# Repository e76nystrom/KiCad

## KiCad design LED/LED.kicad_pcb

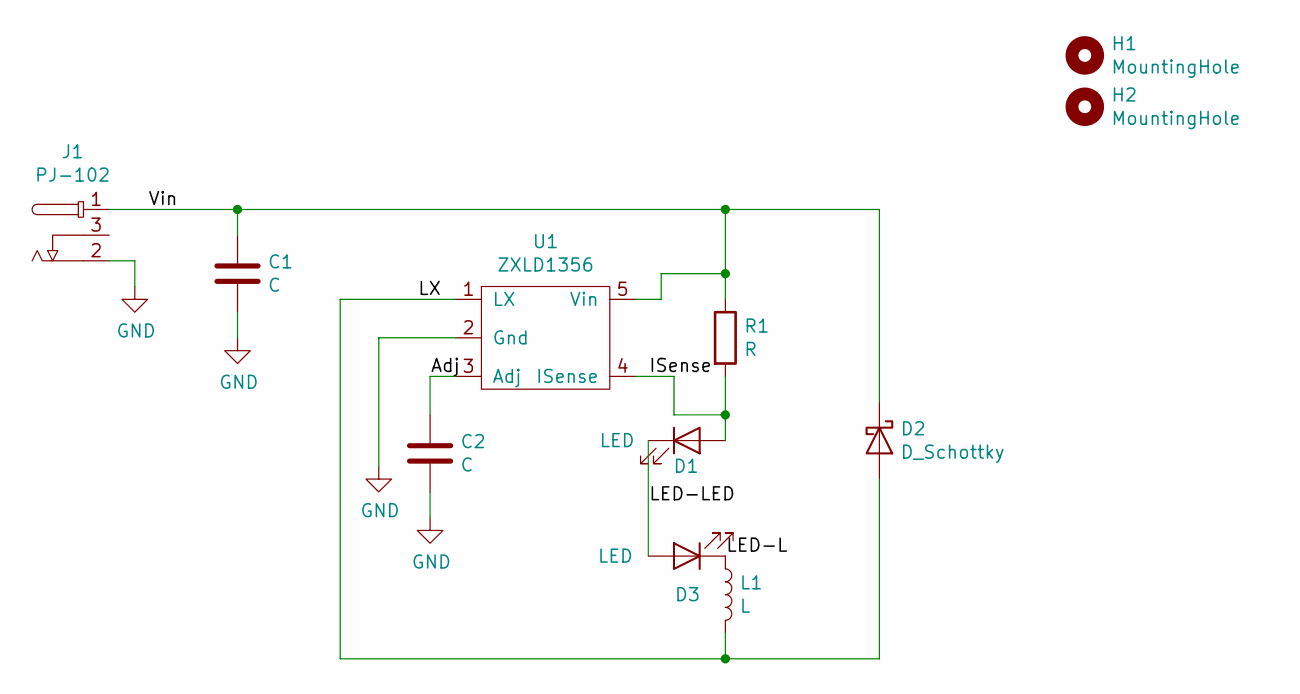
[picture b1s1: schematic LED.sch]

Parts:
C1, C2: C; C_0805_2012Metric_Pad1.15x1.40mm_HandSolder
D1, D3: LED; XT-LED
D2: D_Schottky; D_SMB_Handsoldering
H1, H2: MountingHole; MountingHole _1-8_1-4
J1: PJ-102
L1: L; SDR-1006
R1: R; R_0805_2012Metric_Pad1.15x1.40mm_HandSolder
U1: ZXLD1356; SOT-23-5

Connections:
/Adj: C2.1, U1.3 (Adj)
/ISense: D1.2 (A), R1.2, U1.4 (ISense)
/LED-L: D3.1 (K), L1.1
/LED-LED: D1.1 (K), D3.2 (A)
/LX: D2.2 (A), L1.2, U1.1 (LX)
/Vin: C1.1, D2.1 (K), J1.1, R1.1, U1.5 (Vin)
GND: C1.2, C2.2, J1.2, U1.2 (Gnd)

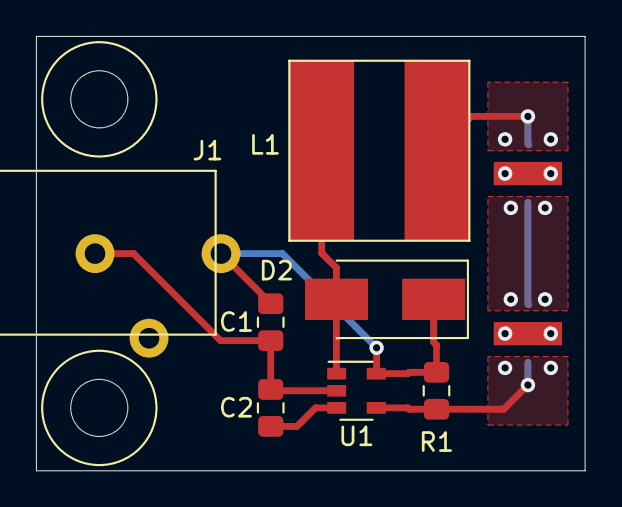
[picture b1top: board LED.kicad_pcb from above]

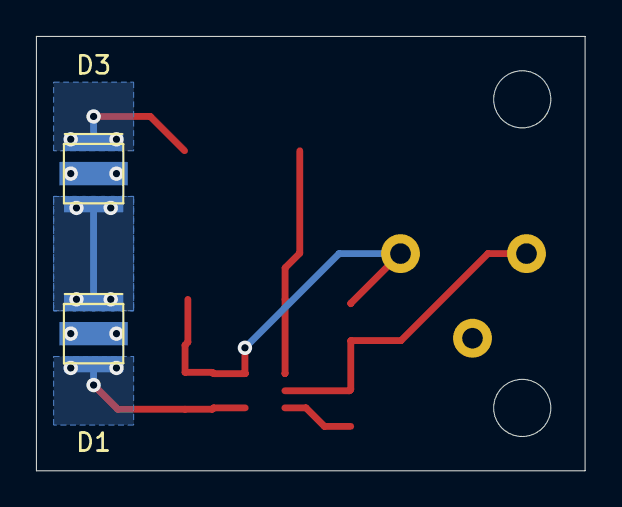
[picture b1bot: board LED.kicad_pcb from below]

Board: 2 copper layers, 30.5 x 24.1 mm, 11 parts (2 on the bottom side), 7 nets.

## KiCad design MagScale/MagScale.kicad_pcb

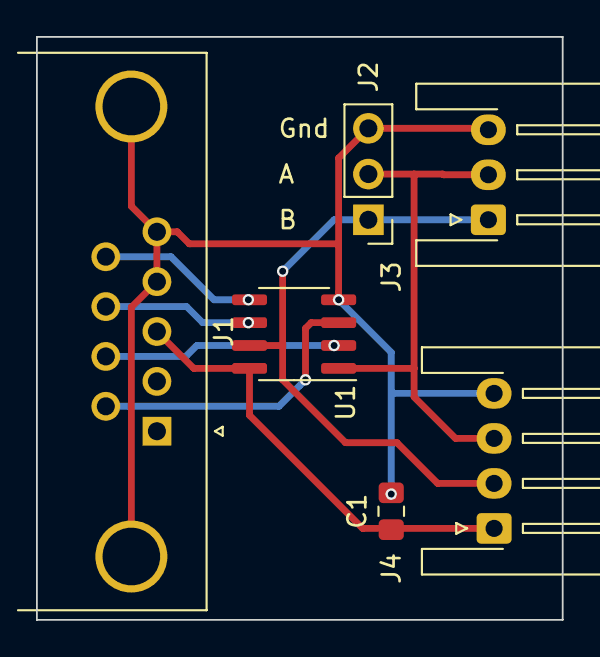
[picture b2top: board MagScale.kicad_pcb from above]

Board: 2 copper layers, 29.2 x 32.4 mm, 6 parts (0 on the bottom side), 8 nets.

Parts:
C1: C; C_0805_2012Metric_Pad1.15x1.40mm_HandSolder
J1: DB9_Female_MountingHoles; DSUB-9_Female_Horizontal_P2.77x2.84mm_EdgePinOffset4.94mm_H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
J2: Conn_01x03_Male; PinHeader_1x03_P2.54mm_Vertical
J3: Conn_01x03; JST_XH_S3B-XH-A-1_1x03_P2.50mm_Horizontal
J4: Conn_01x04; JST_XH_S4B-XH-A-1_1x04_P2.50mm_Horizontal
U1: OP275; SOIC-8_3.9x4.9mm_P1.27mm

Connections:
+5V: C1.1, J1.3, J4.1, U1.8
/A: J2.2, J3.2, J4.3, U1.1
/A+: J1.6, U1.3
/A-: J1.7, U1.2
/B: J2.1, J3.1, J4.2, U1.7
/B+: J1.9, U1.5
/B-: J1.8, U1.6
GND: C1.2, J1.0, J1.4, J1.5, J2.3, J3.3, J4.4, U1.4

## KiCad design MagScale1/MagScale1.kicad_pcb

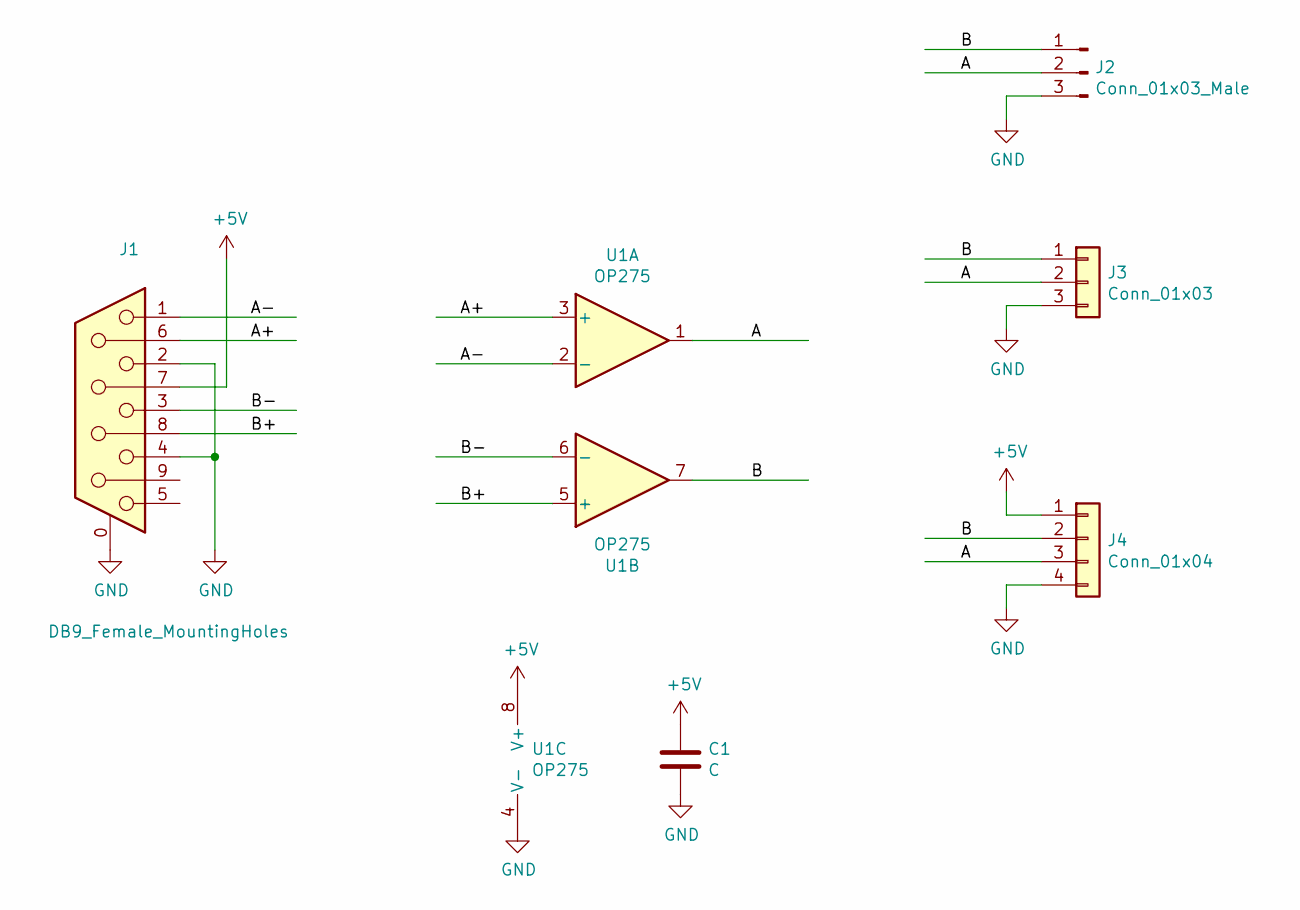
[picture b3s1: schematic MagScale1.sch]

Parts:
C1: C; C_0805_2012Metric_Pad1.15x1.40mm_HandSolder
J1: DB9_Female_MountingHoles; DSUB-9_Female_Horizontal_P2.77x2.84mm_EdgePinOffset4.94mm_H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
J2: Conn_01x03_Male; PinHeader_1x03_P2.54mm_Vertical
J3: Conn_01x03; JST_XH_S3B-XH-A-1_1x03_P2.50mm_Horizontal
J4: Conn_01x04; JST_XH_S4B-XH-A-1_1x04_P2.50mm_Horizontal
U1: OP275; SOIC-8_3.9x4.9mm_P1.27mm

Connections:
+5V: C1.1, J1.7, J4.1, U1.8 (V+)
/A: J2.2, J3.2, J4.3, U1.1
/A+: J1.6, U1.3 (+)
/A-: J1.1, U1.2 (-)
/B: J2.1, J3.1, J4.2, U1.7
/B+: J1.8, U1.5 (+)
/B-: J1.3, U1.6 (-)
GND: C1.2, J1.0 (PAD), J1.2, J1.4, J2.3, J3.3, J4.4, U1.4 (V-)

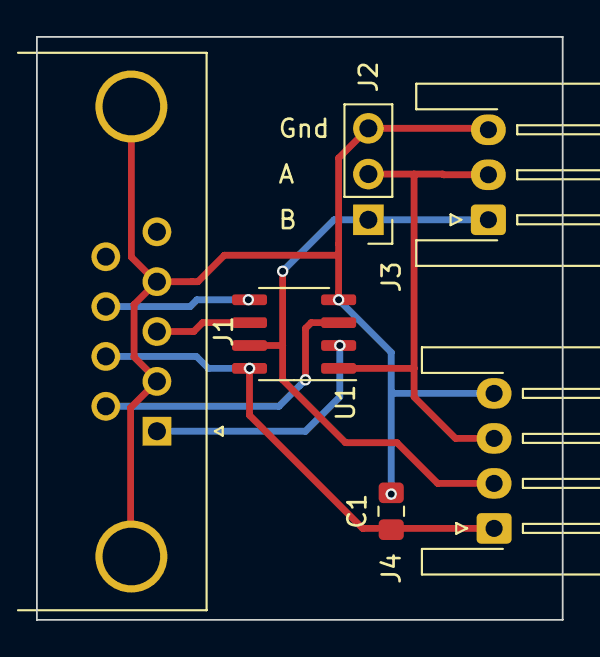
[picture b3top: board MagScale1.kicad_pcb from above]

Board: 2 copper layers, 29.2 x 32.4 mm, 6 parts (0 on the bottom side), 8 nets.

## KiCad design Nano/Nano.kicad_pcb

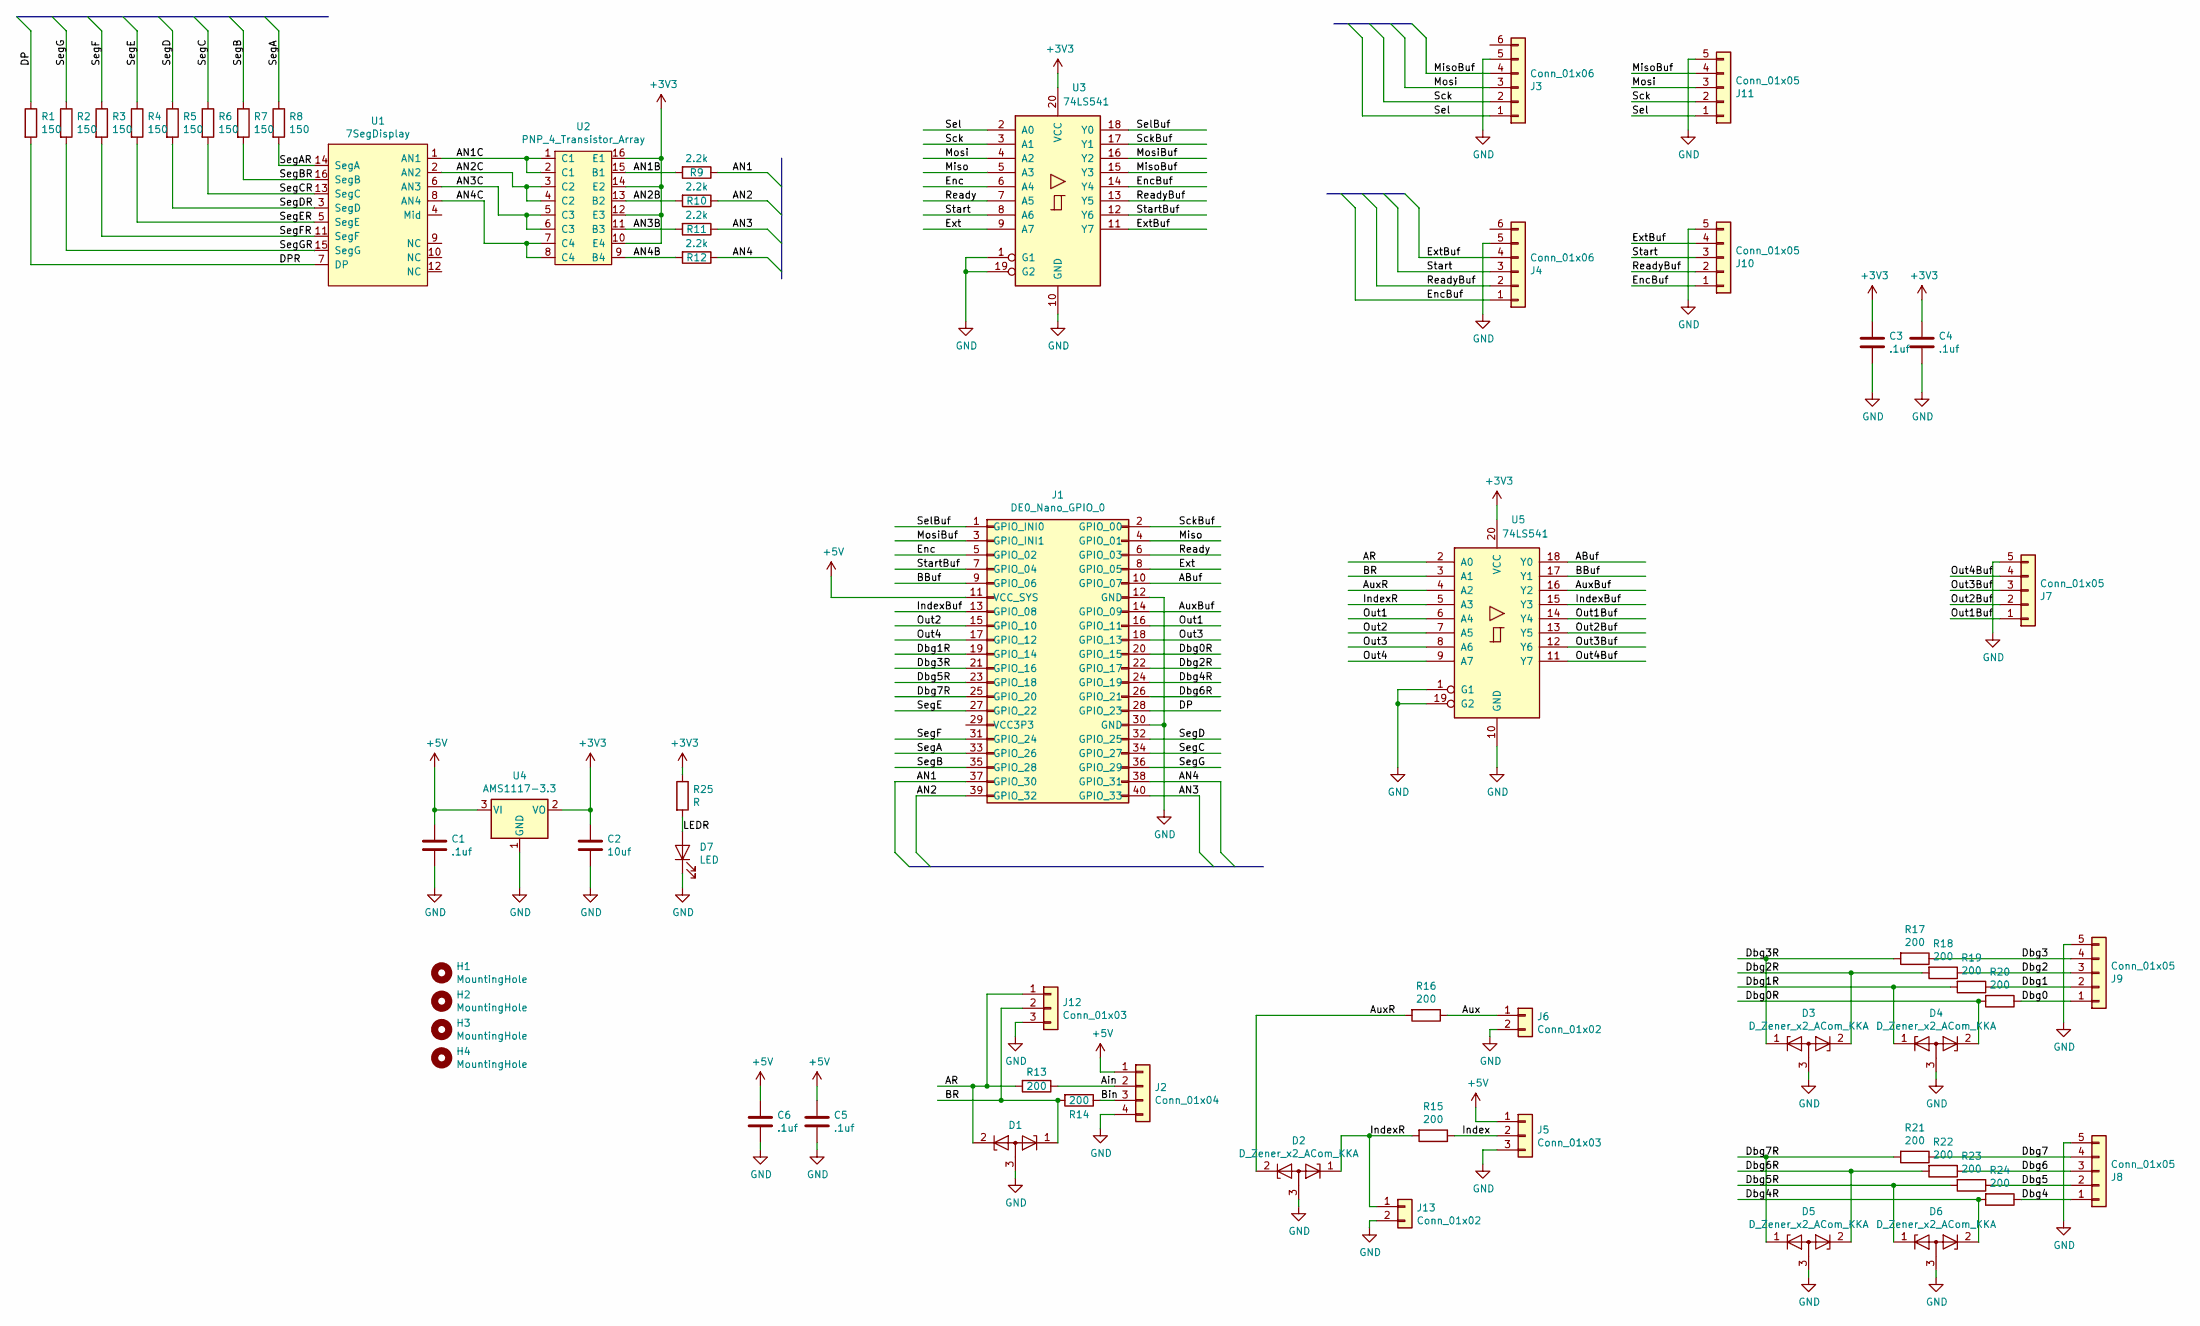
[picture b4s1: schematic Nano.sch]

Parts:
C1, C3, C4, C5, C6: .1uf; C_0805_2012Metric_Pad1.15x1.40mm_HandSolder
C2: 10uf; C_0805_2012Metric_Pad1.15x1.40mm_HandSolder
D1, D2, D3, D4, D5, D6: D_Zener_x2_ACom_KKA; SOT-23-Handsoldering
D7: LED; LED_0805_2012Metric_Pad1.15x1.40mm_HandSolder
H1, H2, H3, H4: MountingHole; MountingHole _1-8_1-4
J1: DE0_Nano_GPIO_0; PinHeader_2x20_P2.54mm_Vertical
J2: Conn_01x04; JST_EH_S4B-EH_1x04_P2.50mm_Horizontal
J3, J4: Conn_01x06; PinHeader_1x06_P2.54mm_Horizontal
J5: Conn_01x03; JST_EH_S3B-EH_1x03_P2.50mm_Horizontal
J6, J13: Conn_01x02; PinHeader_1x02_P2.54mm_Vertical
J7, J8, J9, J10, J11: Conn_01x05; PinHeader_1x05_P2.54mm_Vertical
J12: Conn_01x03; PinHeader_1x03_P2.54mm_Vertical
R1, R2, R3, R4, R5, R6, R7, R8: 150; R_0805_2012Metric_Pad1.15x1.40mm_HandSolder
R9, R10, R11, R12: 2.2k; R_0805_2012Metric_Pad1.15x1.40mm_HandSolder
R13, R14, R15, R16, R17, R18, R19, R20, R21, R22, R23, R24: 200; R_0805_2012Metric_Pad1.15x1.40mm_HandSolder
R25: R; R_0805_2012Metric_Pad1.15x1.40mm_HandSolder
U1: 7SegDisplay; 4_Digit_LED
U2: PNP_4_Transistor_Array; SOIC-16_5.6mm
U3, U5: 74LS541; SOIC-20W_7.5x12.8mm_P1.27mm
U4: AMS1117-3.3; SOT-223-3_TabPin2

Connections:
+3V3: C2.1, C3.1, C4.1, R25.1, U2.10 (E4), U2.12 (E3), U2.14 (E2), U2.16 (E1), U3.20 (VCC), U4.2 (VO), U5.20 (VCC)
+5V: C1.1, C5.1, C6.1, J1.11 (VCC_SYS), J2.1, J5.1, U4.3 (VI)
/ABuf: J1.10 (GPIO_07), U5.18 (Y0)
/AN1: J1.37 (GPIO_30), R9.1
/AN1B: R9.2, U2.15 (B1)
/AN1C: U1.1 (AN1), U2.1 (C1), U2.2 (C1)
/AN2: J1.39 (GPIO_32), R10.1
/AN2B: R10.2, U2.13 (B2)
/AN2C: U1.2 (AN2), U2.3 (C2), U2.4 (C2)
/AN3: J1.40 (GPIO_33), R11.1
/AN3B: R11.2, U2.11 (B3)
/AN3C: U1.6 (AN3), U2.5 (C3), U2.6 (C3)
/AN4: J1.38 (GPIO_31), R12.1
/AN4B: R12.2, U2.9 (B4)
/AN4C: U1.8 (AN4), U2.7 (C4), U2.8 (C4)
/AR: D1.2 (K), J12.1, R13.2, U5.2 (A0)
/Ain: J2.2, R13.1
/Aux: J6.1, R16.1
/AuxBuf: J1.14 (GPIO_09), U5.16 (Y2)
/AuxR: D2.2 (K), R16.2, U5.4 (A2)
/BBuf: J1.9 (GPIO_06), U5.17 (Y1)
/BR: D1.1 (K), J12.2, R14.2, U5.3 (A1)
/Bin: J2.3, R14.1
/DP: J1.28 (GPIO_23), R1.1
/DPR: R1.2, U1.7 (DP)
/Dbg0: J9.1, R20.1
/Dbg0R: D4.2 (K), J1.20 (GPIO_15), R20.2
/Dbg1: J9.2, R19.1
/Dbg1R: D4.1 (K), J1.19 (GPIO_14), R19.2
/Dbg2: J9.3, R18.1
/Dbg2R: D3.2 (K), J1.22 (GPIO_17), R18.2
/Dbg3: J9.4, R17.1
/Dbg3R: D3.1 (K), J1.21 (GPIO_16), R17.2
/Dbg4: J8.1, R24.1
/Dbg4R: D6.2 (K), J1.24 (GPIO_19), R24.2
/Dbg5: J8.2, R23.1
/Dbg5R: D6.1 (K), J1.23 (GPIO_18), R23.2
/Dbg6: J8.3, R22.1
/Dbg6R: D5.2 (K), J1.26 (GPIO_21), R22.2
/Dbg7: J8.4, R21.1
/Dbg7R: D5.1 (K), J1.25 (GPIO_20), R21.2
/Enc: J1.5 (GPIO_02), U3.6 (A4)
/EncBuf: J4.1, J10.1, U3.14 (Y4)
/Ext: J1.8 (GPIO_05), U3.9 (A7)
/ExtBuf: J4.4, J10.4, U3.11 (Y7)
/Index: J5.2, R15.1
/IndexBuf: J1.13 (GPIO_08), U5.15 (Y3)
/IndexR: D2.1 (K), J13.1, R15.2, U5.5 (A3)
/LEDR: D7.2 (A), R25.2
/Miso: J1.4 (GPIO_01), U3.5 (A3)
/MisoBuf: J3.4, J11.4, U3.15 (Y3)
/Mosi: J3.3, J11.3, U3.4 (A2)
/MosiBuf: J1.3 (GPIO_INI1), U3.16 (Y2)
/Out1: J1.16 (GPIO_11), U5.6 (A4)
/Out1Buf: J7.1, U5.14 (Y4)
/Out2: J1.15 (GPIO_10), U5.7 (A5)
/Out2Buf: J7.2, U5.13 (Y5)
/Out3: J1.18 (GPIO_13), U5.8 (A6)
/Out3Buf: J7.3, U5.12 (Y6)
/Out4: J1.17 (GPIO_12), U5.9 (A7)
/Out4Buf: J7.4, U5.11 (Y7)
/Ready: J1.6 (GPIO_03), U3.7 (A5)
/ReadyBuf: J4.2, J10.2, U3.13 (Y5)
/Sck: J3.2, J11.2, U3.3 (A1)
/SckBuf: J1.2 (GPIO_00), U3.17 (Y1)
/SegA: J1.33 (GPIO_26), R8.1
/SegAR: R8.2, U1.14 (SegA)
/SegB: J1.35 (GPIO_28), R7.1
/SegBR: R7.2, U1.16 (SegB)
/SegC: J1.34 (GPIO_27), R6.1
/SegCR: R6.2, U1.13 (SegC)
/SegD: J1.32 (GPIO_25), R5.1
/SegDR: R5.2, U1.3 (SegD)
/SegE: J1.27 (GPIO_22), R4.1
/SegER: R4.2, U1.5 (SegE)
/SegF: J1.31 (GPIO_24), R3.1
/SegFR: R3.2, U1.11 (SegF)
/SegG: J1.36 (GPIO_29), R2.1
/SegGR: R2.2, U1.15 (SegG)
/Sel: J3.1, J11.1, U3.2 (A0)
/SelBuf: J1.1 (GPIO_INI0), U3.18 (Y0)
/Start: J4.3, J10.3, U3.8 (A6)
/StartBuf: J1.7 (GPIO_04), U3.12 (Y6)
GND: C1.2, C2.2, C3.2, C4.2, C5.2, C6.2, D1.3 (A), D2.3 (A), D3.3 (A), D4.3 (A), D5.3 (A), D6.3 (A), D7.1 (K), J1.12 (GND), J1.30 (GND), J2.4, J3.5, J4.5, J5.3, J6.2, J7.5, J8.5, J9.5, J10.5, J11.5, J12.3, J13.2, U3.1 (G1), U3.10 (GND), U3.19 (G2), U4.1 (GND), U5.1 (G1), U5.10 (GND), U5.19 (G2)

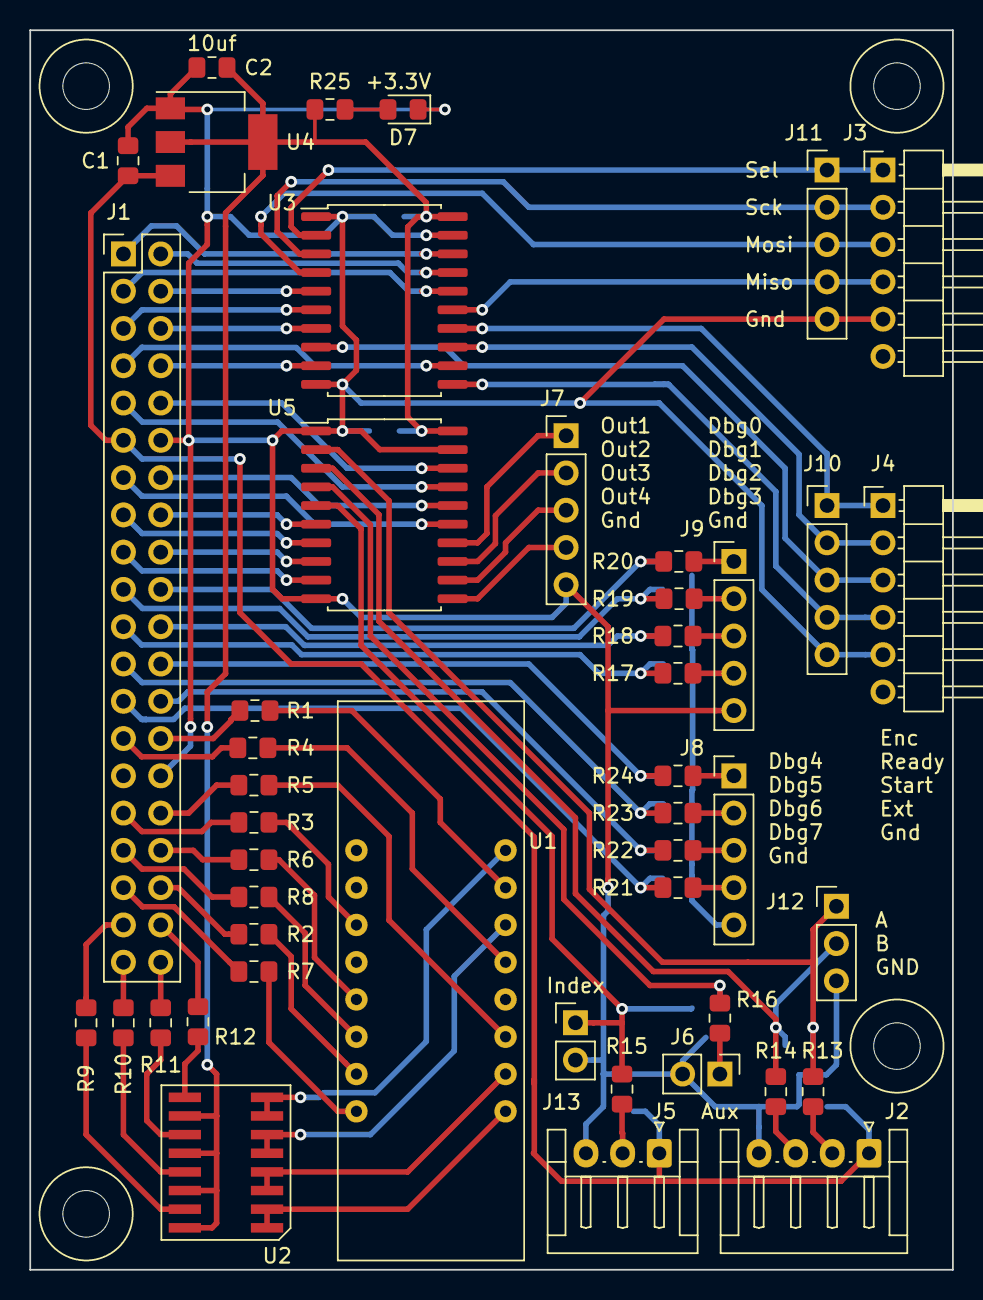
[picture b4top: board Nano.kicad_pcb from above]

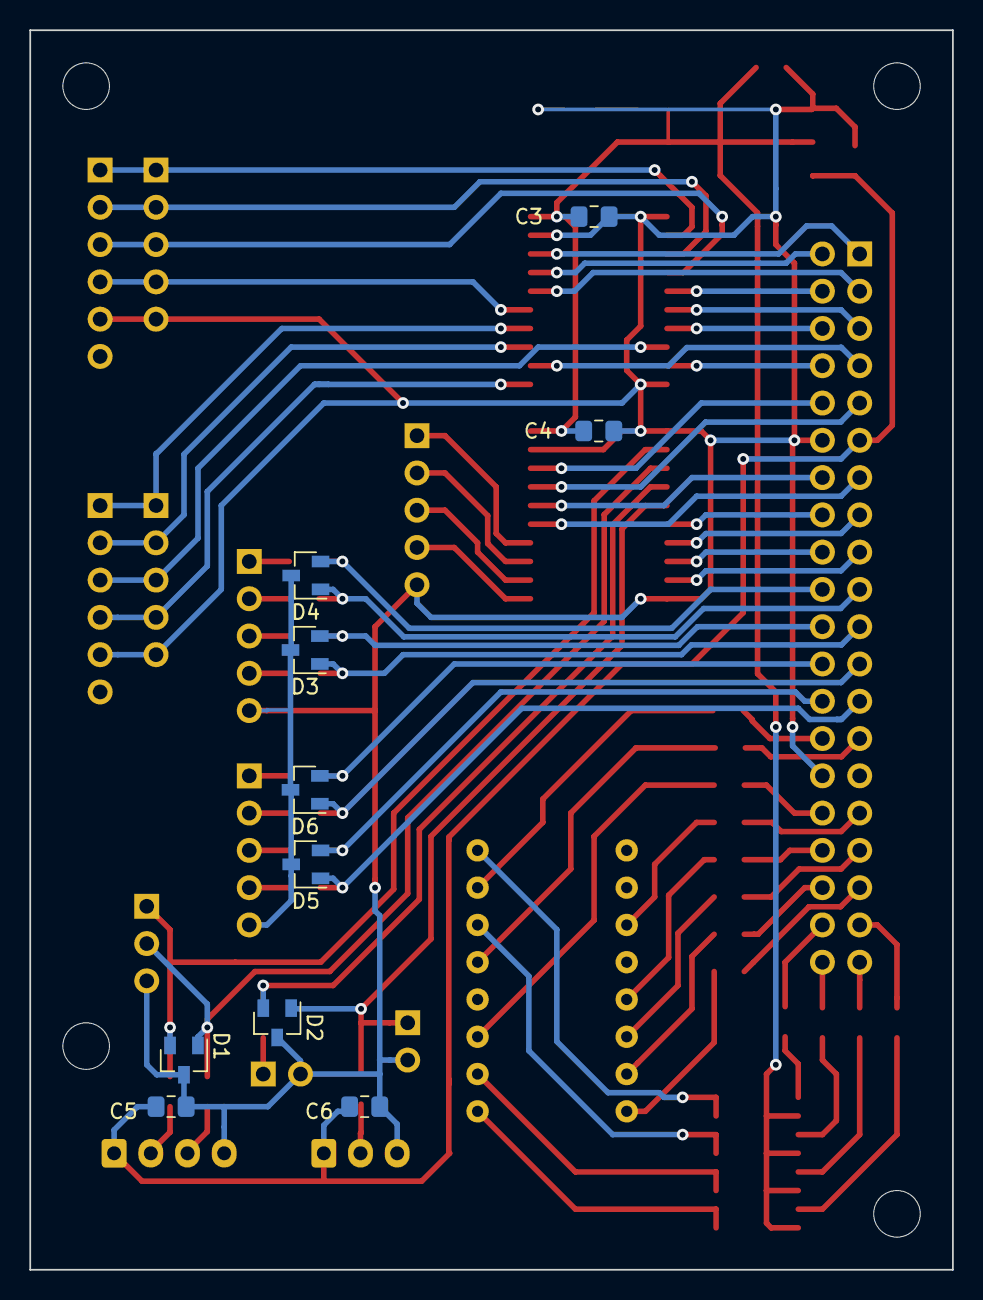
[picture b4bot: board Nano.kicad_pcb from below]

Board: 2 copper layers, 62.9 x 84.5 mm, 60 parts (10 on the bottom side), 84 nets.

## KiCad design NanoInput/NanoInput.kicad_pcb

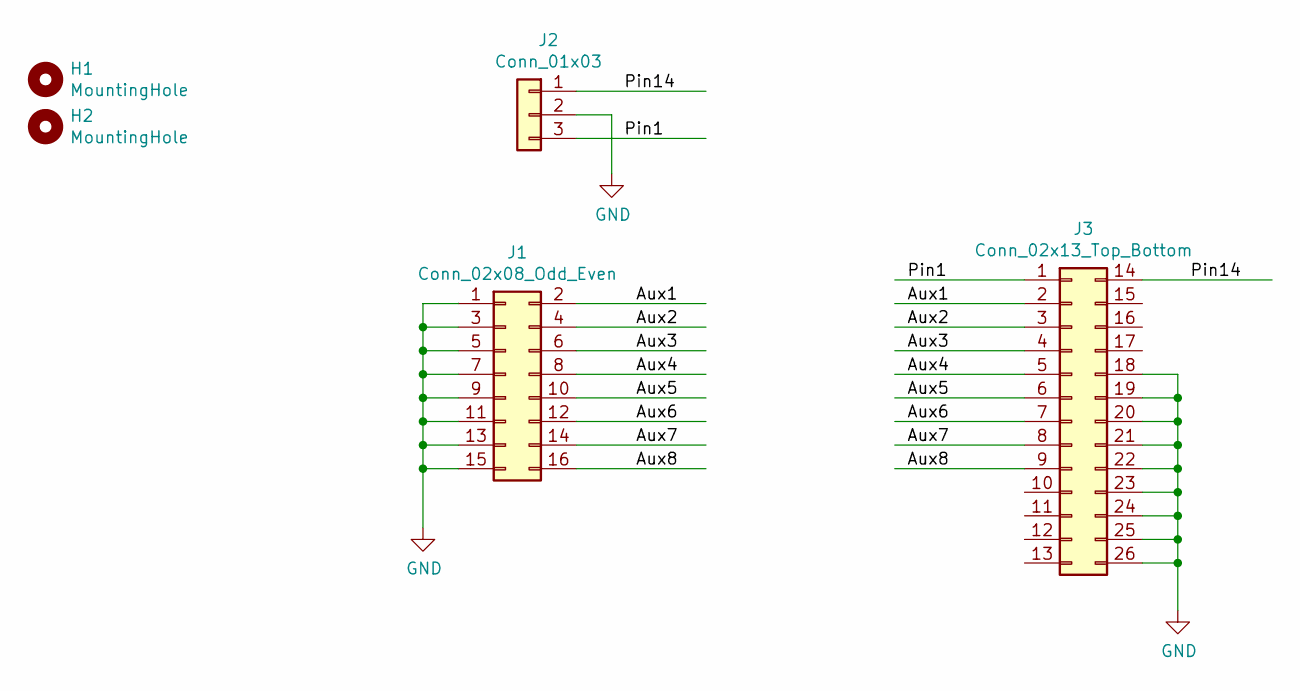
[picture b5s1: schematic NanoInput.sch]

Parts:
H1, H2: MountingHole; MountingHole _1-8_1-4
J1: Conn_02x08_Odd_Even; PinHeader_2x08_P2.54mm_Vertical
J2: Conn_01x03; JST_EH_S3B-EH_1x03_P2.50mm_Horizontal
J3: Conn_02x13_Top_Bottom; PinHeader_2x13_P2.54mm_Vertical

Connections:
/Aux1: J1.2, J3.2
/Aux2: J1.4, J3.3
/Aux3: J1.6, J3.4
/Aux4: J1.8, J3.5
/Aux5: J1.10, J3.6
/Aux6: J1.12, J3.7
/Aux7: J1.14, J3.8
/Aux8: J1.16, J3.9
/Pin1: J2.3, J3.1
/Pin14: J2.1, J3.14
GND: J1.1, J1.3, J1.5, J1.7, J1.9, J1.11, J1.13, J1.15, J2.2, J3.18, J3.19, J3.20, J3.21, J3.22, J3.23, J3.24, J3.25, J3.26

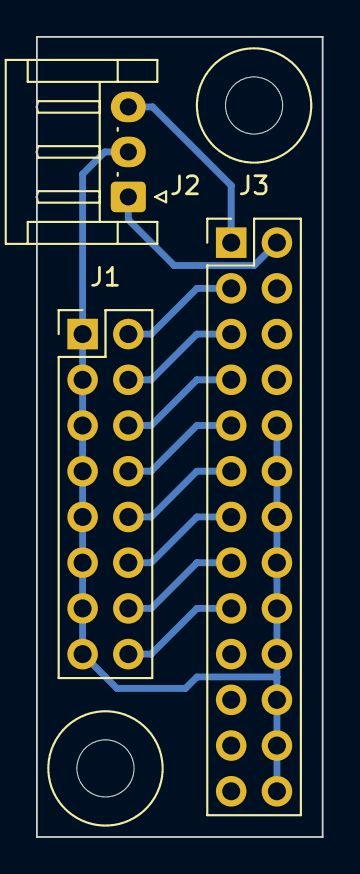
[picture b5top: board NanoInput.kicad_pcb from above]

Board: 2 copper layers, 15.9 x 44.5 mm, 5 parts (0 on the bottom side), 11 nets.

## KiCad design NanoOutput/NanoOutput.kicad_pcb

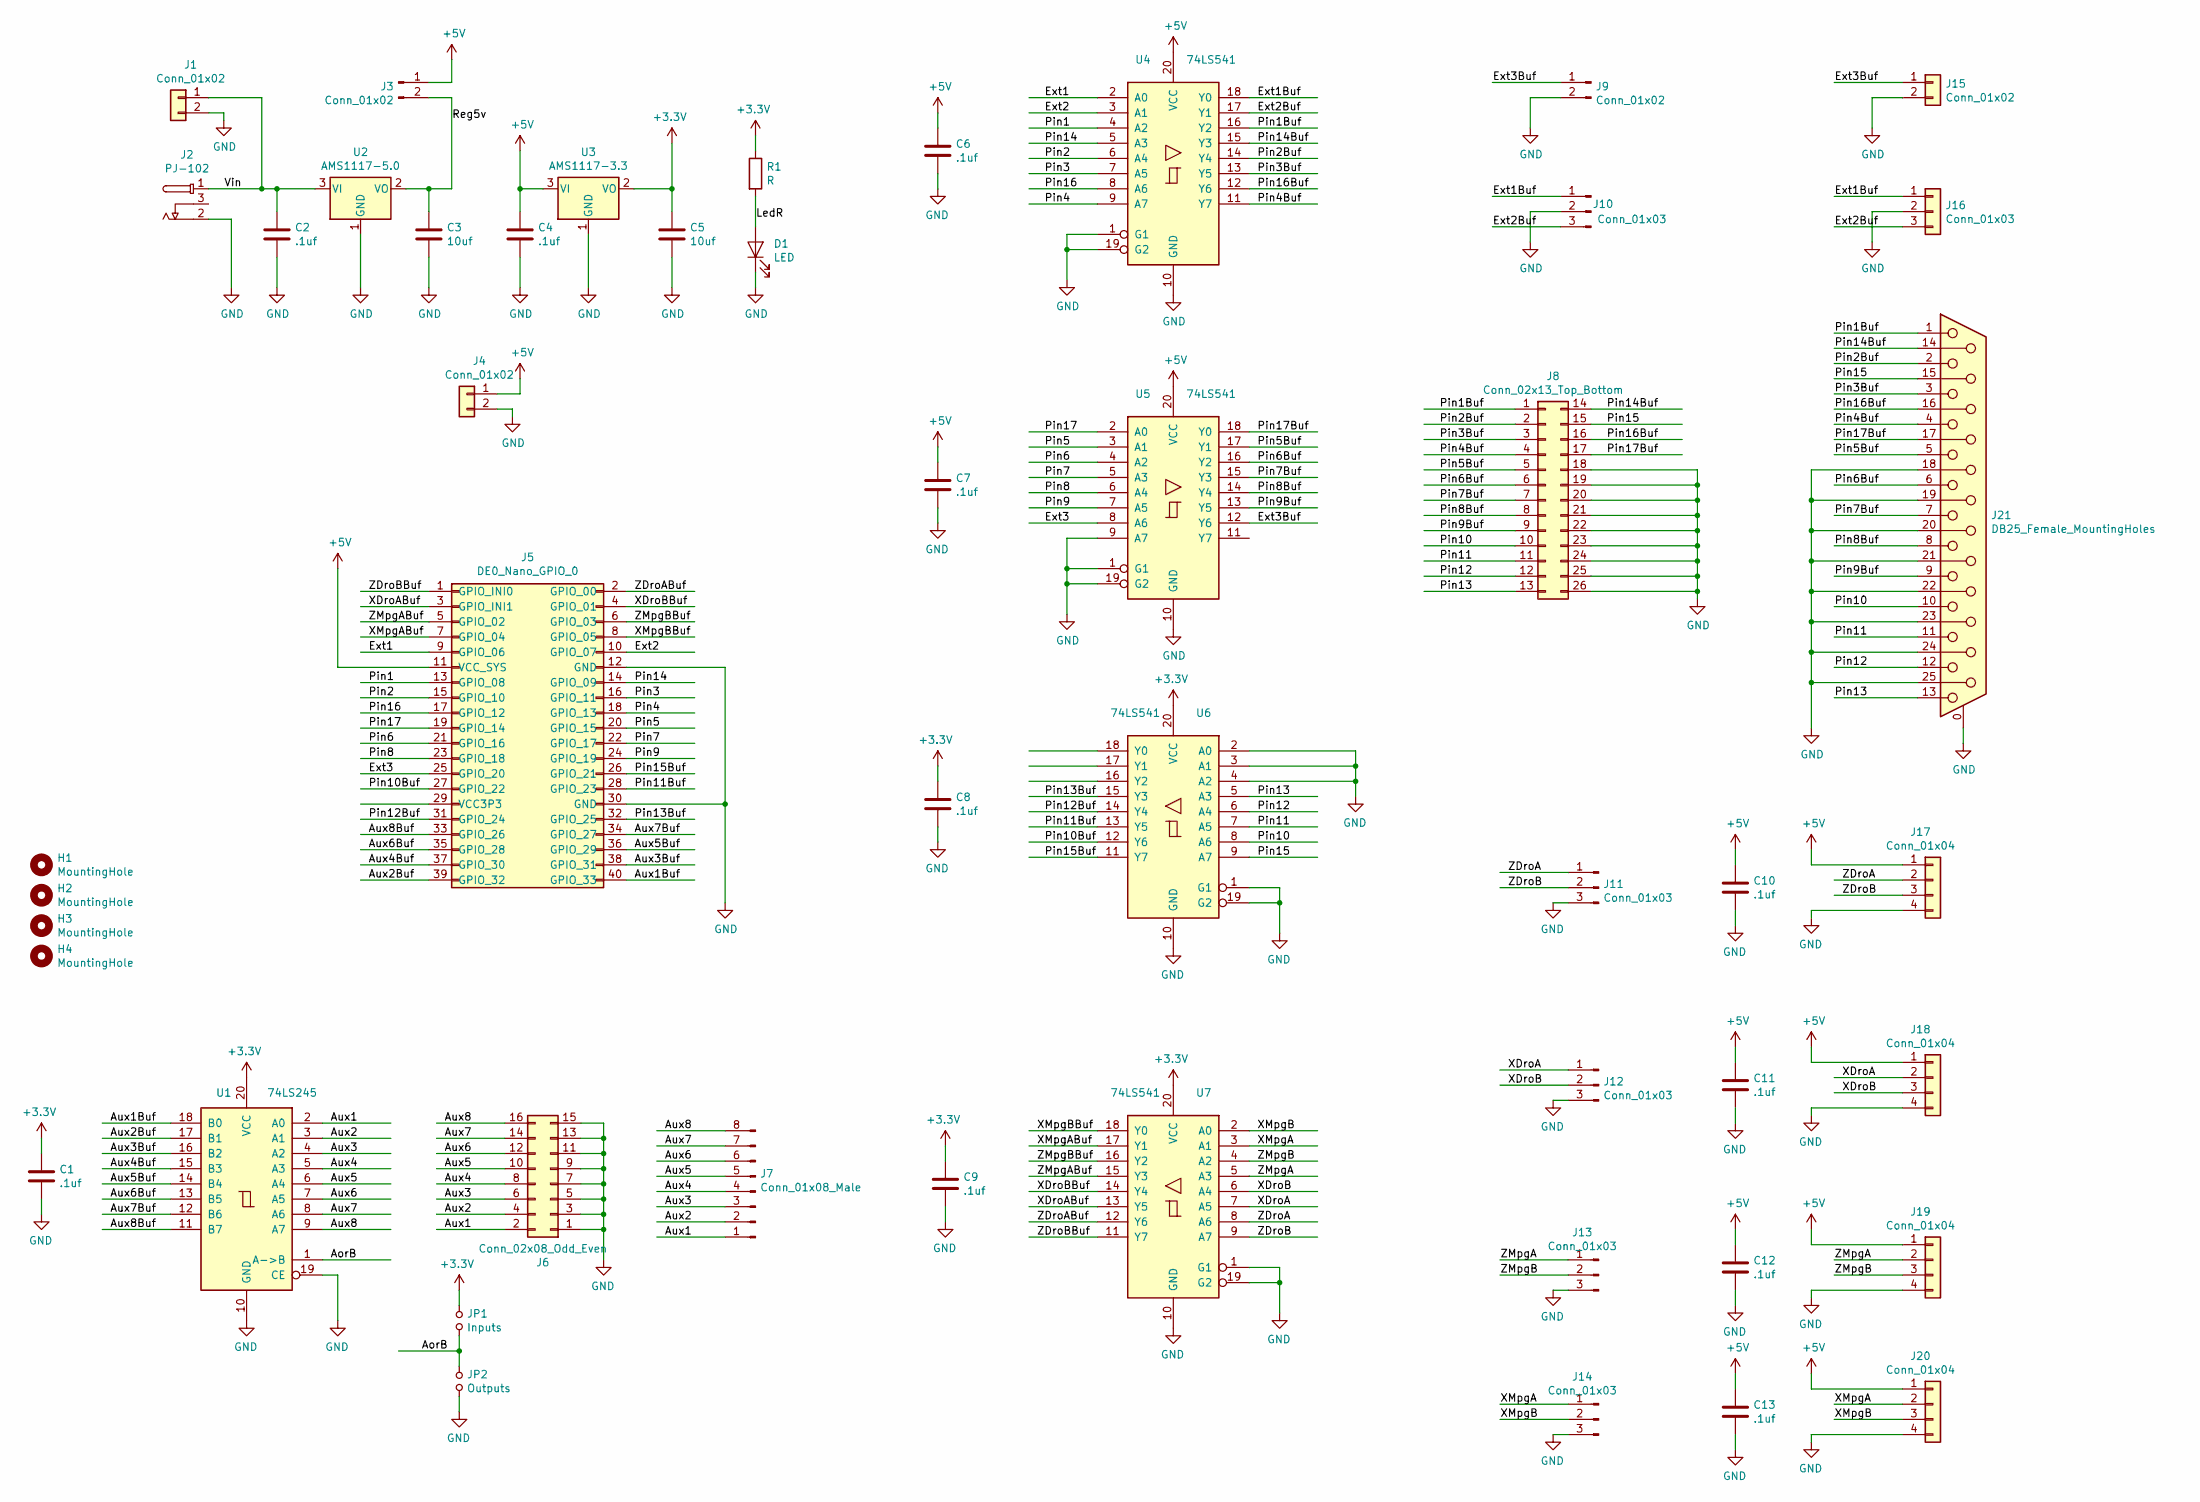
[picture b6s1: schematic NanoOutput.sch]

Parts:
C1, C2, C4, C6, C7, C8, C9, C10, C11, C12, C13: .1uf; C_0805_2012Metric_Pad1.15x1.40mm_HandSolder
C3, C5: 10uf; C_0805_2012Metric_Pad1.15x1.40mm_HandSolder
D1: LED; D_0805_2012Metric_Pad1.15x1.40mm_HandSolder
H1, H2, H3, H4: MountingHole; MountingHole _1-8_1-4
J1: Conn_01x02; 2 Pin 3.81mm
J2: PJ-102
J3, J15: Conn_01x02; PinHeader_1x02_P2.54mm_Vertical
J4: Conn_01x02; JST_EH_B2B-EH-A_1x02_P2.50mm_Vertical
J5: DE0_Nano_GPIO_0; PinHeader_2x20_P2.54mm_Vertical
J6: Conn_02x08_Odd_Even; PinHeader_2x08_P2.54mm_Vertical
J7: Conn_01x08_Male; PinHeader_1x08_P2.54mm_Vertical
J8: Conn_02x13_Top_Bottom; PinHeader_2x13_P2.54mm_Vertical
J9: Conn_01x02; JST_EH_S2B-EH_1x02_P2.50mm_Horizontal
J10: Conn_01x03; JST_EH_S3B-EH_1x03_P2.50mm_Horizontal
J11, J12, J13, J14, J16: Conn_01x03; PinHeader_1x03_P2.54mm_Vertical
J17, J18, J19, J20: Conn_01x04; JST_EH_S4B-EH_1x04_P2.50mm_Horizontal
J21: DB25_Female_MountingHoles; DSUB-25_Female_Horizontal_P2.77x2.84mm_EdgePinOffset4.94mm_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
JP1: Inputs; R_0603_1608Metric_Pad1.05x0.95mm_HandSolder
JP2: Outputs; R_0603_1608Metric_Pad1.05x0.95mm_HandSolder
R1: R; R_0805_2012Metric_Pad1.15x1.40mm_HandSolder
U1: 74LS245; SOIC-20W_7.5x12.8mm_P1.27mm
U2: AMS1117-5.0; SOT-223-3_TabPin2
U3: AMS1117-3.3; SOT-89-3_Handsoldering
U4, U5, U6, U7: 74LS541; SOIC-20W_7.5x12.8mm_P1.27mm

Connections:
+3V3: C1.1, C5.1, C8.1, C9.1, JP1.1, R1.1, U1.20 (VCC), U3.2 (VO), U6.20 (VCC), U7.20 (VCC)
+5V: C4.1, C6.1, C7.1, C10.1, C11.1, C12.1, C13.1, J3.1, J4.1, J5.11 (VCC_SYS), J17.1, J18.1, J19.1, J20.1, U3.3 (VI), U4.20 (VCC), U5.20 (VCC)
/AorB: JP1.2, JP2.1, U1.1 (A->B)
/Aux1: J6.2, J7.1, U1.2 (A0)
/Aux1Buf: J5.40 (GPIO_33), U1.18 (B0)
/Aux2: J6.4, J7.2, U1.3 (A1)
/Aux2Buf: J5.39 (GPIO_32), U1.17 (B1)
/Aux3: J6.6, J7.3, U1.4 (A2)
/Aux3Buf: J5.38 (GPIO_31), U1.16 (B2)
/Aux4: J6.8, J7.4, U1.5 (A3)
/Aux4Buf: J5.37 (GPIO_30), U1.15 (B3)
/Aux5: J6.10, J7.5, U1.6 (A4)
/Aux5Buf: J5.36 (GPIO_29), U1.14 (B4)
/Aux6: J6.12, J7.6, U1.7 (A5)
/Aux6Buf: J5.35 (GPIO_28), U1.13 (B5)
/Aux7: J6.14, J7.7, U1.8 (A6)
/Aux7Buf: J5.34 (GPIO_27), U1.12 (B6)
/Aux8: J6.16, J7.8, U1.9 (A7)
/Aux8Buf: J5.33 (GPIO_26), U1.11 (B7)
/Ext1: J5.9 (GPIO_06), U4.2 (A0)
/Ext1Buf: J10.1, J16.1, U4.18 (Y0)
/Ext2: J5.10 (GPIO_07), U4.3 (A1)
/Ext2Buf: J10.3, J16.3, U4.17 (Y1)
/Ext3: J5.25 (GPIO_20), U5.8 (A6)
/Ext3Buf: J9.1, J15.1, U5.12 (Y6)
/LedR: D1.2 (A), R1.2
/Pin1: J5.13 (GPIO_08), U4.4 (A2)
/Pin1Buf: J8.1, J21.1, U4.16 (Y2)
/Pin2: J5.15 (GPIO_10), U4.6 (A4)
/Pin2Buf: J8.2, J21.2, U4.14 (Y4)
/Pin3: J5.16 (GPIO_11), U4.7 (A5)
/Pin3Buf: J8.3, J21.3, U4.13 (Y5)
/Pin4: J5.18 (GPIO_13), U4.9 (A7)
/Pin4Buf: J8.4, J21.4, U4.11 (Y7)
/Pin5: J5.20 (GPIO_15), U5.3 (A1)
/Pin5Buf: J8.5, J21.5, U5.17 (Y1)
/Pin6: J5.21 (GPIO_16), U5.4 (A2)
/Pin6Buf: J8.6, J21.6, U5.16 (Y2)
/Pin7: J5.22 (GPIO_17), U5.5 (A3)
/Pin7Buf: J8.7, J21.7, U5.15 (Y3)
/Pin8: J5.23 (GPIO_18), U5.6 (A4)
/Pin8Buf: J8.8, J21.8, U5.14 (Y4)
/Pin9: J5.24 (GPIO_19), U5.7 (A5)
/Pin9Buf: J8.9, J21.9, U5.13 (Y5)
/Pin10: J8.10, J21.10, U6.8 (A6)
/Pin10Buf: J5.27 (GPIO_22), U6.12 (Y6)
/Pin11: J8.11, J21.11, U6.7 (A5)
/Pin11Buf: J5.28 (GPIO_23), U6.13 (Y5)
/Pin12: J8.12, J21.12, U6.6 (A4)
/Pin12Buf: J5.31 (GPIO_24), U6.14 (Y4)
/Pin13: J8.13, J21.13, U6.5 (A3)
/Pin13Buf: J5.32 (GPIO_25), U6.15 (Y3)
/Pin14: J5.14 (GPIO_09), U4.5 (A3)
/Pin14Buf: J8.14, J21.14, U4.15 (Y3)
/Pin15: J8.15, J21.15, U6.9 (A7)
/Pin15Buf: J5.26 (GPIO_21), U6.11 (Y7)
/Pin16: J5.17 (GPIO_12), U4.8 (A6)
/Pin16Buf: J8.16, J21.16, U4.12 (Y6)
/Pin17: J5.19 (GPIO_14), U5.2 (A0)
/Pin17Buf: J8.17, J21.17, U5.18 (Y0)
/Reg5v: C3.1, J3.2, U2.2 (VO)
/Vin: C2.1, J1.1, J2.1, U2.3 (VI)
/XDroA: J12.1, J18.2, U7.7 (A5)
/XDroABuf: J5.3 (GPIO_INI1), U7.13 (Y5)
/XDroB: J12.2, J18.3, U7.6 (A4)
/XDroBBuf: J5.4 (GPIO_01), U7.14 (Y4)
/XMpgA: J14.1, J20.2, U7.3 (A1)
/XMpgABuf: J5.7 (GPIO_04), U7.17 (Y1)
/XMpgB: J14.2, J20.3, U7.2 (A0)
/XMpgBBuf: J5.8 (GPIO_05), U7.18 (Y0)
/ZDroA: J11.1, J17.2, U7.8 (A6)
/ZDroABuf: J5.2 (GPIO_00), U7.12 (Y6)
/ZDroB: J11.2, J17.3, U7.9 (A7)
/ZDroBBuf: J5.1 (GPIO_INI0), U7.11 (Y7)
/ZMpgA: J13.1, J19.2, U7.5 (A3)
/ZMpgABuf: J5.5 (GPIO_02), U7.15 (Y3)
/ZMpgB: J13.2, J19.3, U7.4 (A2)
/ZMpgBBuf: J5.6 (GPIO_03), U7.16 (Y2)
GND: C1.2, C2.2, C3.2, C4.2, C5.2, C6.2, C7.2, C8.2, C9.2, C10.2, C11.2, C12.2, C13.2, D1.1 (K), J1.2, J2.2, J4.2, J5.12 (GND), J5.30 (GND), J6.1, J6.3, J6.5, J6.7, J6.9, J6.11, J6.13, J6.15, J8.18, J8.19, J8.20, J8.21, J8.22, J8.23, J8.24, J8.25, J8.26, J9.2, J10.2, J11.3, J12.3, J13.3, J14.3, J15.2, J16.2, J17.4, J18.4, J19.4, J20.4, J21.0 (PAD), J21.18, J21.19, J21.20, J21.21, J21.22, J21.23, J21.24, J21.25, JP2.2, U1.10 (GND), U1.19 (CE), U2.1 (GND), U3.1 (GND), U4.1 (G1), U4.10 (GND), U4.19 (G2), U5.1 (G1), U5.9 (A7), U5.10 (GND), U5.19 (G2), U6.1 (G1), U6.2 (A0), U6.3 (A1), U6.4 (A2), U6.10 (GND), U6.19 (G2), U7.1 (G1), U7.10 (GND), U7.19 (G2)
